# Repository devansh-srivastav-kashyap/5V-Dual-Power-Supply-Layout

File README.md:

# 5V-Dual-Power-Supply-Circuit Board

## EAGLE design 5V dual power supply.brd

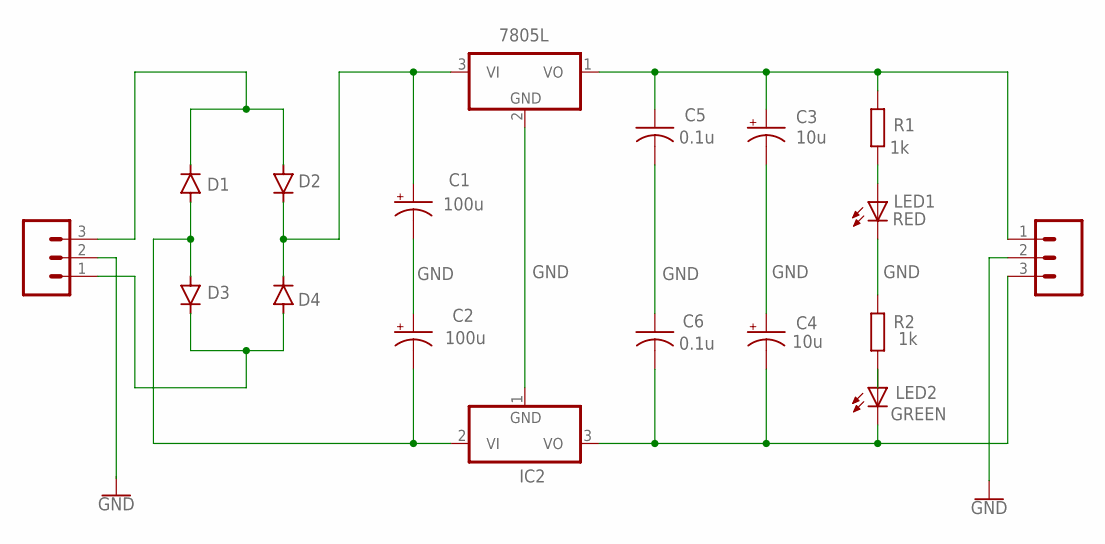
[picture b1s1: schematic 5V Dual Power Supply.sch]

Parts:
C1, C2: 100u; E2-4
C3, C4: 10u; E2-4
C5, C6: 0.1u; C025-025X050
D1, D2, D3, D4: 1N4004; DO41-10
IC1: 7805L; TO92
IC2: 7905L; TO92
J1, J4: CONN_03-SCREW-5MM; SCREWTERMINAL-5MM-3
LED1: RED; LED5MM
LED2: GREEN; LED5MM
R1, R2: 1k; 0204/7

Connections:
GND: C1.-, C2.+, C3.-, C4.+, C5.2, C6.1, IC1.2 (GND), IC2.1 (GND), J1.2, J4.2, LED1.K (C), R2.2
unnamed: D1.C, D2.A, J1.3
unnamed: C1.+, D2.C, D4.C, IC1.3 (VI)
unnamed: D3.C, D4.A, J1.1
unnamed: C3.+, C5.1, IC1.1 (VO), J4.1, R1.2
unnamed: C4.-, C6.2, IC2.3 (VO), J4.3, LED2.K (C)
unnamed: LED1.A, R1.1
unnamed: LED2.A, R2.1
unnamed: C2.-, D1.A, D3.A, IC2.2 (VI)

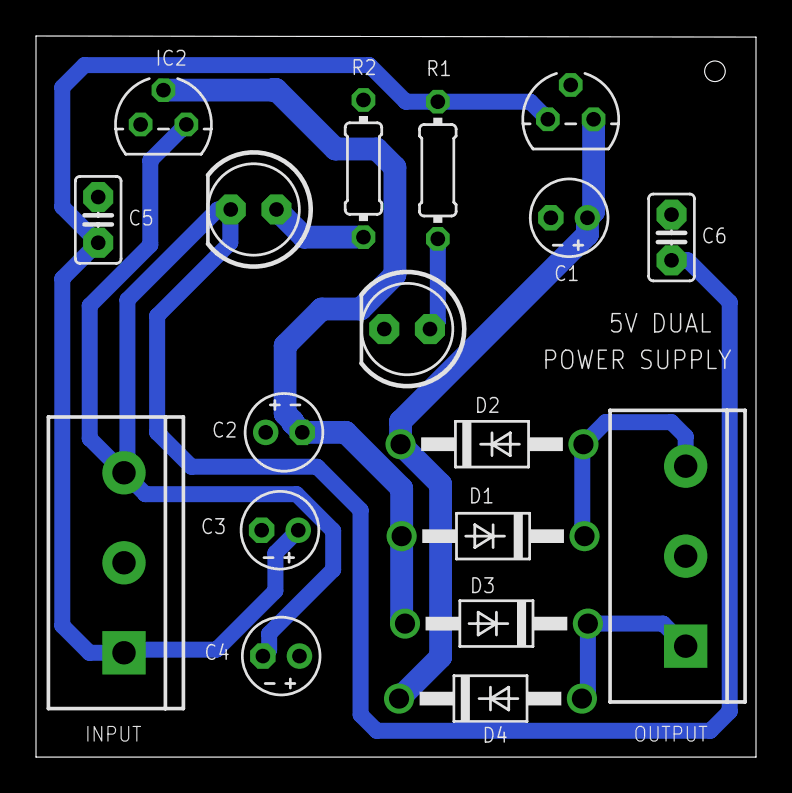
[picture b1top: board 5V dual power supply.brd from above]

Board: 2 copper layers, 40.0 x 40.1 mm, 18 parts (0 on the bottom side), 9 nets.

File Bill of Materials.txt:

Partlist exported from C:/Documents/EAGLE/projects/Disneyo/Disneyo/untitled.sch at 29-09-2021 13:52

Qty Value  Device            Package             Parts          Description                                                                                                     POPULARITY PROD_ID    SF_SKU    SPICEPREFIX
1          7905L             TO92                IC2            Negative VOLTAGE REGULATOR                                                                                      0                                          
2          CONN_03-SCREW-5MM SCREWTERMINAL-5MM-3 J1, J4         Multi connection point. Often used as Generic Header-pin footprint for 0.1 inch spaced/style header connections            CONN-10134 PRT-08433            
2   0.1u   C-US025-025X050   C025-025X050        C5, C6         CAPACITOR, American symbol                                                                                                                                 
2   100u   CPOL-USE2-4       E2-4                C1, C2         POLARIZED CAPACITOR, American symbol                                                                                                                       
2   10u    CPOL-USE2-4       E2-4                C3, C4         POLARIZED CAPACITOR, American symbol                                                                                                                       
4   1N4004 1N4004            DO41-10             D1, D2, D3, D4 DIODE                                                                                                           82                                         
2   1k     R-EU_0204/7       0204/7              R1, R2         RESISTOR, European symbol                                                                                       79                              R          
1   7805L  7805L             TO92                IC1            Positive VOLTAGE REGULATOR                                                                                      0                                          
1   GREEN  LED5MM            LED5MM              LED2           LED                                                                                                                                                        
1   RED    LED5MM            LED5MM              LED1           LED

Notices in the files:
parts and their libraries:
SparkFun-Connectors: Licensing: Creative Commons ShareAlike 4.0 International - https://creativecommons.org/licenses/by-sa/4.0
